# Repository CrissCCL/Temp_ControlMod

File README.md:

# 🔥 Temperature Control Module
### From System Identification to Real-Time Embedded Control

🚀 **Featured by Arduino**  
[Read the official article](https://blog.arduino.cc/2026/02/26/from-theory-to-hardware-cristian-castro-lagos-on-control-engineering-with-arduino/)

Engineering-grade closed-loop temperature control platform integrating ARX system identification, digital PI controller design, deterministic real-time implementation, and experimental validation using Arduino Leonardo.

## 🔎 Why This Project Matters

This platform demonstrates the complete professional workflow used in real-world control system development:

Data acquisition → System identification → Controller design → Discretization → Embedded implementation → Experimental validation.

It bridges control theory with physical hardware under real sampling, saturation, and noise constraints.

## 📖 Overview
This low-cost module was designed and built to perform hands-on experiments in Digital Control. The system is controlled using an Arduino Leonardo, heat is modulated with a TIP31C transistor, and temperature is measured using a TMP36 sensor.  

It provides a simple and practical platform for learning control theory in a laboratory environment.

## 📂 Contents
- `/HardwareV2` → New Version schematic, Gerbers and BOM+POS for PCBA.
- `/Hardware` → schematic, PCB, Gerbers.
- `/control_temp_LC` → C code for Arduino.

## 🌐 YouTube
📺 [Part 1 [ES]](https://youtu.be/2oqOS14WYN8?si=qGYRzMjagaLqCLr8)

## 📊 Project Status

| Component | Status |
|------------|--------|
| Temperature Sensor Interface | ✅ Completed |
| Signal Filtering and Smoothing | ✅ Completed |
| PID Control Implementation | ✅ Completed |
| Migration from MATLAB Data Logging to Processing 4 GUI | ✅ Completed |
| Data Storage and CSV Export | ✅ Completed  |
| Processing 4 GUI (Monitoring & Logging) | ✅ Completed |
|  PCB Design with Improved Measurement Stability  | ✅ Completed |

> 💻 The project now features a Processing 4 graphical interface that replaces the previous MATLAB-based monitoring, data recording and data logging system.  
> 🔧 This new GUI allows real-time temperature monitoring and data recording, alongside the ongoing development of a custom PCB to improve measurement stability and reduce signal noise.

## ⚙️ System Description
- **Controller:** Arduino Leonardo or Mega  
- **Sensor:** TMP36 analog temperature sensor  
- **Actuator:** TIP31C transistor controlling a heating element  
- **Control Strategy:** Digital PI temperature regulation  
- **Sampling period:** 0.1 seconds  
- **Data transmission:** Serial communication for data logging and Processing 4 GUI monitoring  
- **PCB:** Custom-designed board for power and measurement stability  

## 🔄 Control Loop

### Controlled Variables
- **Temperature** → Temperature value control (stabilization)

## 📐 Digital PID Control

The PID controllers implemented in this project are **incremental (velocity form)** and use **trapezoidal integration** for the integral term.  
This ensures:
- Accurate discrete-time implementation suitable for microcontrollers.
- Consistency between simulation and embedded hardware behavior.
- Avoidance of integral windup when combined with actuator saturation or anti-windup mechanisms.

The Module uses a discrete PI controller implemented on a Arduino microcontroller.  
The control law in the digital domain is expressed as:

$$
u(n) = u(n-1) + K_0 e(n) + K_1 e(n-1)
$$

Digital PI controller implemented for temperature measured,

$$
V_{PWM}(n) = V_{PWM}(n-1) + K_0 e(n) + K_1 e(n-1)
$$

### Parameters:
The parameters are adjusted for temperature measured,

$$
K_0 = K_p + \frac{K_p}{2T_i} T_s
$$

$$
K_1 = -K_p + \frac{K_p}{2T_i} T_s
$$

## 🔉 Signal Processing: Low-Pass IIR Filter (1st Order)

To reduce measurement noise, a **first-order IIR low-pass filter** was applied to the temperature signal before feeding it to the controller and the ARX model.  

### 🔹 Filter Equation  

$$
y(k) =(1 - \alpha)  \cdot x(k) +  \alpha \cdot y(k-1)
$$  

Where:  
- $$x(k)$$: raw sensor measurement at time step $$k$$  
- $$y(k)$$: filtered output  
- $$\alpha$$: smoothing factor, $$(0<\alpha<1)$$ 

## 🧪 PI Control Test and ARX Model Comparison  

A test was performed using a **PI controller** applied to the temperature control module.  
The experimental results were compared against a **linear ARX model** identified from system data.  

### 🔹 General ARX Model Equation  

The ARX (Auto-Regressive with eXogenous input) model is defined as:  

$$
y(k) + a_1 y(k-1) + a_2 y(k-2) + \dots + a_{n_a} y(k-n_a) =
b_1 u(k-1) + b_2 u(k-2) + \dots + b_{n_b} u(k-n_b) + e(k)
$$  

Where:  
- $$y(k)$$: system output at sample $$k$$ 
- $$u(k)$$: input signal at sample $$k$$  
- $$( a_i, b_j)$$: ARX parameters  
- $$( n_a, n_b)$$: model orders  
- $$e(k) $$: disturbance/noise  

### 🔹 Results Overview  
- ✅ The PI controller improved **temperature tracking** and reduced overshoot.  
- 📉 The ARX model captured the main dynamics, with small discrepancies due to nonlinear heat transfer effects.  
- ⚖️ The comparison confirms the applicability of ARX models for **thermal system control design**.  

### 🔹 Experimental Plots  

## 🖥️ GUI — Monitoring and Data Logging

The graphical user interface (GUI) shown in the photograph is developed using **Processing 4**.  
It is designed **only for monitoring** the temperature module in real time and for **recording experimental data**.  

Key features:
- Real-time plot of temperature and setpoint.
- Display of control output (PWM or equivalent).
- Logging of measurements to files for offline analysis.
- Simple visualization of system behavior during experiments.

> ⚠️ **Note:** The GUI is for observation and data recording only; it does **not** modify the control system or send commands to the hardware.

> ⚠️ **Status:** Work In Progress — the GUI is being actively developed and will be added to the repository once sufficiently stable.

## 📉 Measurement Stability Improvement — PCB v2 vs PCB v3

The new PCB revision focused on improving the **temperature signal stability** without changing the control algorithm.

### 🔧 Issues Observed in PCB v2
In the previous revision, the temperature reading from the TMP36 sensor showed perturbations during heater actuation by the TIP31C transistor.  
This was mainly due to lack of proper analog stabilization near the sensor.

### ✅ Modifications Introduced in PCB v3
To address this, the following hardware changes were implemented according to TMP36 manufacturer guidelines:

- ✔ **Decoupling capacitor added** close to TMP36 power pins
- ✔ **Analog conditioning resistors changed to SMD**
- ✔ **All related passive components migrated to SMD footprint** to minimize parasitics and noise pickup

No changes were made to the controller firmware or sensor type — only the PCB-level conditioning was improved.

### 📊 Comparative Experimental Results

| Version | Condition | Plot |
|--------|------------|------|
| **PCB v2 (Old)** | Visible ripple & switching noise on temperature signal |  |
| **PCB v3 (New)** | Stable and smooth measurement — disturbances eliminated |  |

> ✅ The addition of the capacitor and SMD passives significantly reduced noise, improving the quality of temperature measurements and the overall stability of the closed-loop response.

## 🖼️ Render 3D PCB 

<table>
  <tr>
    <td align="center">
      <br>
      <sub>PCB Render - Version 3 - NEW VERSION </sub>
    </td>
    <td align="center">
        <br>
      <sub>PCB Render - Version 2- OLDER VERSION </sub>
    </td>
  </tr>
</table>

## ⚡ Physical Prototype

The updated PCB and system assembly have been tested successfully.  
The following image shows the complete setup of the **new prototype version**:

The following images show the complete setup of the **previous prototype version**:

<table>
  <tr>
    <td align="center">
      <br>
      <sub>Device connections</sub>
    </td>
    <td align="center">
      <br>
      <sub>Complete setup</sub>
    </td>
  </tr>
</table>

## 🔗 ROS 2 Integration

This embedded temperature control module can be connected to a ROS 2 system
for supervision, telemetry streaming, remote setpoint control and online metrics.

👉 **ROS 2 Bridge Repository:**  
[Ros integration](https://github.com/CrissCCL/Temp_ControlMod_ROS_integration)

The ROS integration provides:

- UART ↔ ROS 2 bridge
- Real-time topics (/temp, /u, /ref)
- Remote setpoint commands
- Online control performance metrics (IAE, ISE, ITAE, etc.)
- rosbag logging and visualization tools

This separation keeps:
- this repo → embedded/firmware/control
- ROS repo → middleware/supervision/integration

## 🔗 Related Repositories

For additional tutorials and examples related to digital control simulations, visit:

- [Digital Control — Anti-Windup (Positional PI)](https://github.com/CrissCCL/Digital_ControlAntiWindup)
- [Digital Control Simulation — First Order System + Saturation](https://github.com/CrissCCL/Digital_ControlSim)
- [Digital Control Simulation — ARX Model + Saturation](https://github.com/CrissCCL/Digital_ControlSimARX)

## 🤝 Support projects
 Support me on Patreon [https://www.patreon.com/c/CrissCCL](https://www.patreon.com/c/CrissCCL)

## 📜 License
MIT License

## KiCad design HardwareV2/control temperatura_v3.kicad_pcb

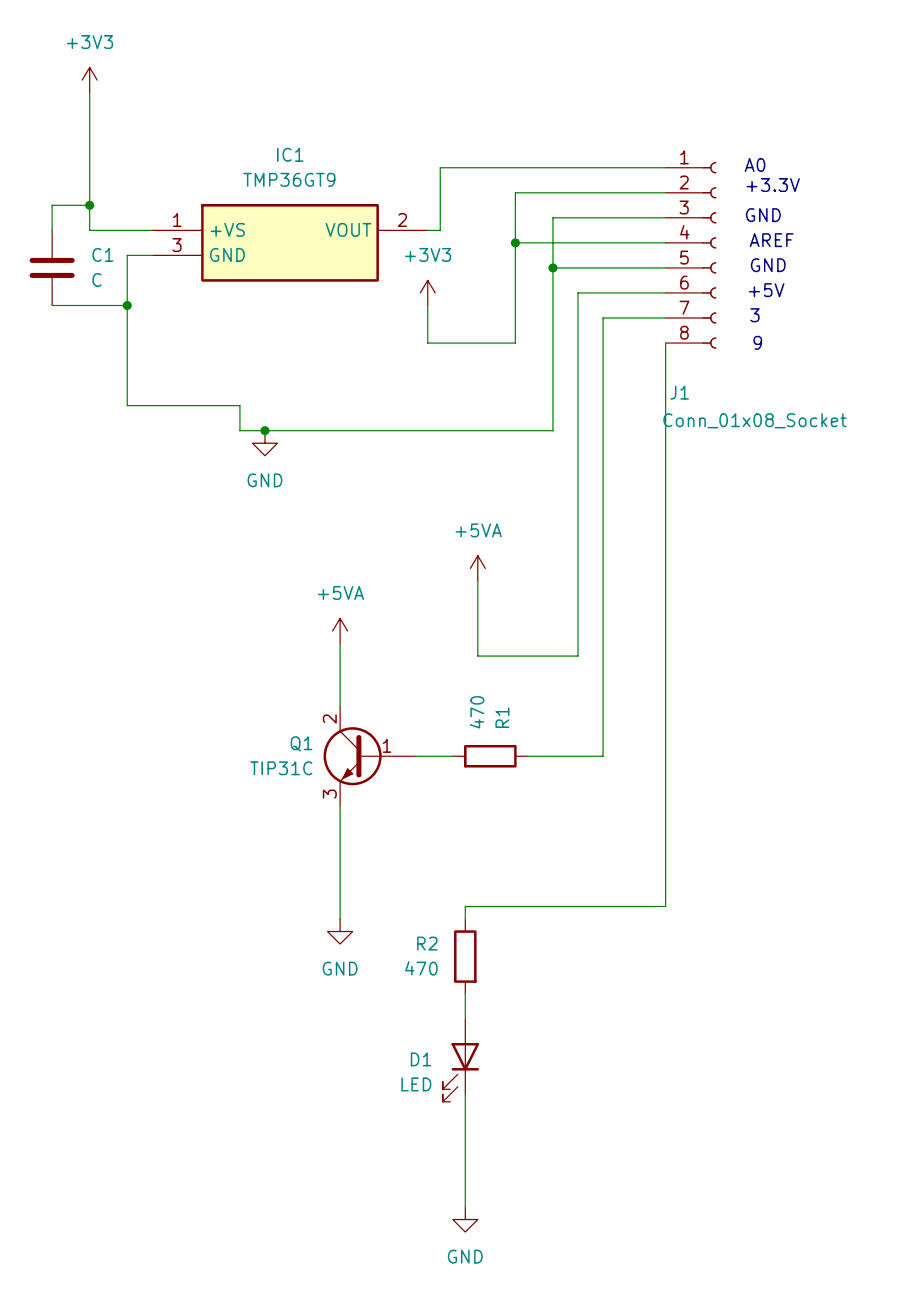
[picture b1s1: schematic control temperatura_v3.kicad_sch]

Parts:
C1: C; C_1206_3216Metric_Pad1.33x1.80mm_HandSolder
D1: LED; LED_D5.0mm
IC1: TMP36GT9; Manufacturer_Part_Number TMP36GT9; Mouser Part Number 584-TMP36GT9
J1: Conn_01x08_Socket; PinHeader_1x08_P2.54mm_Vertical
Q1: TIP31C; TO-220-3_Vertical
R1, R2: 470; R_1206_3216Metric_Pad1.30x1.75mm_HandSolder

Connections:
+3V3: C1.1, IC1.1 (+VS), J1.2, J1.4
+5VA: J1.6, Q1.2 (C)
GND: C1.2, D1.1 (K), IC1.3 (GND), J1.3, J1.5, Q1.3 (E)
unnamed: D1.2 (A), R2.2
unnamed: IC1.2 (VOUT), J1.1
unnamed: J1.7, R1.1
unnamed: J1.8, R2.1
unnamed: Q1.1 (B), R1.2

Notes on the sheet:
+5V
GND
+3.3V
AREF

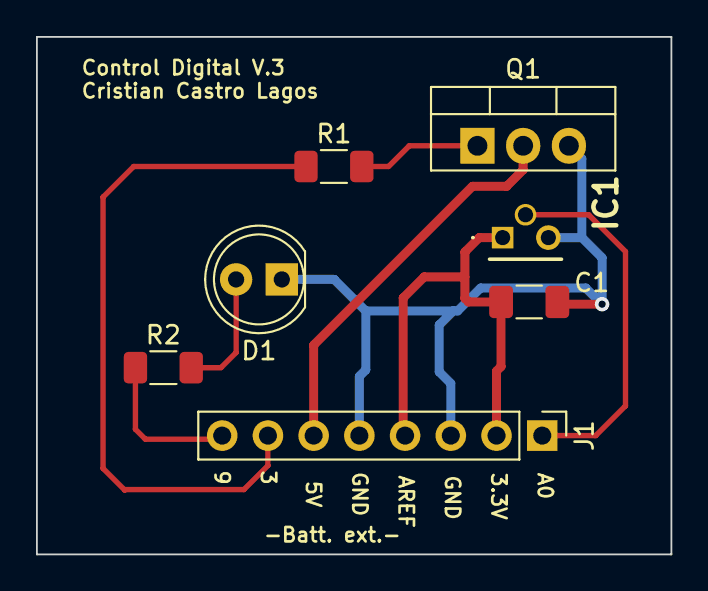
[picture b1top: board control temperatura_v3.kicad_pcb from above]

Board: 2 copper layers, 35.2 x 28.8 mm, 7 parts (0 on the bottom side), 8 nets.

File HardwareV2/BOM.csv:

"Reference","Qty","Value","DNP","Exclude from BOM","Exclude from Board","Footprint","Datasheet"
"C1","1","C","","","","Capacitor_SMD:C_1206_3216Metric_Pad1.33x1.80mm_HandSolder","~"
"D1","1","LED","","","","LED_THT:LED_D5.0mm","~"
"IC1","1","TMP36GT9","","","","SamacSys_Parts:TMP36GT9","https://www.analog.com/media/en/technical-documentation/data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"
"J1","1","Conn_01x08_Socket","","","","Connector_PinHeader_2.54mm:PinHeader_1x08_P2.54mm_Vertical","~"
"Q1","1","TIP31C","","","","Package_TO_SOT_THT:TO-220-3_Vertical","https://www.centralsemi.com/get_document.php?cmp=1&mergetype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"
"R1,R2","2","470","","","","Resistor_SMD:R_1206_3216Metric_Pad1.30x1.75mm_HandSolder","~"

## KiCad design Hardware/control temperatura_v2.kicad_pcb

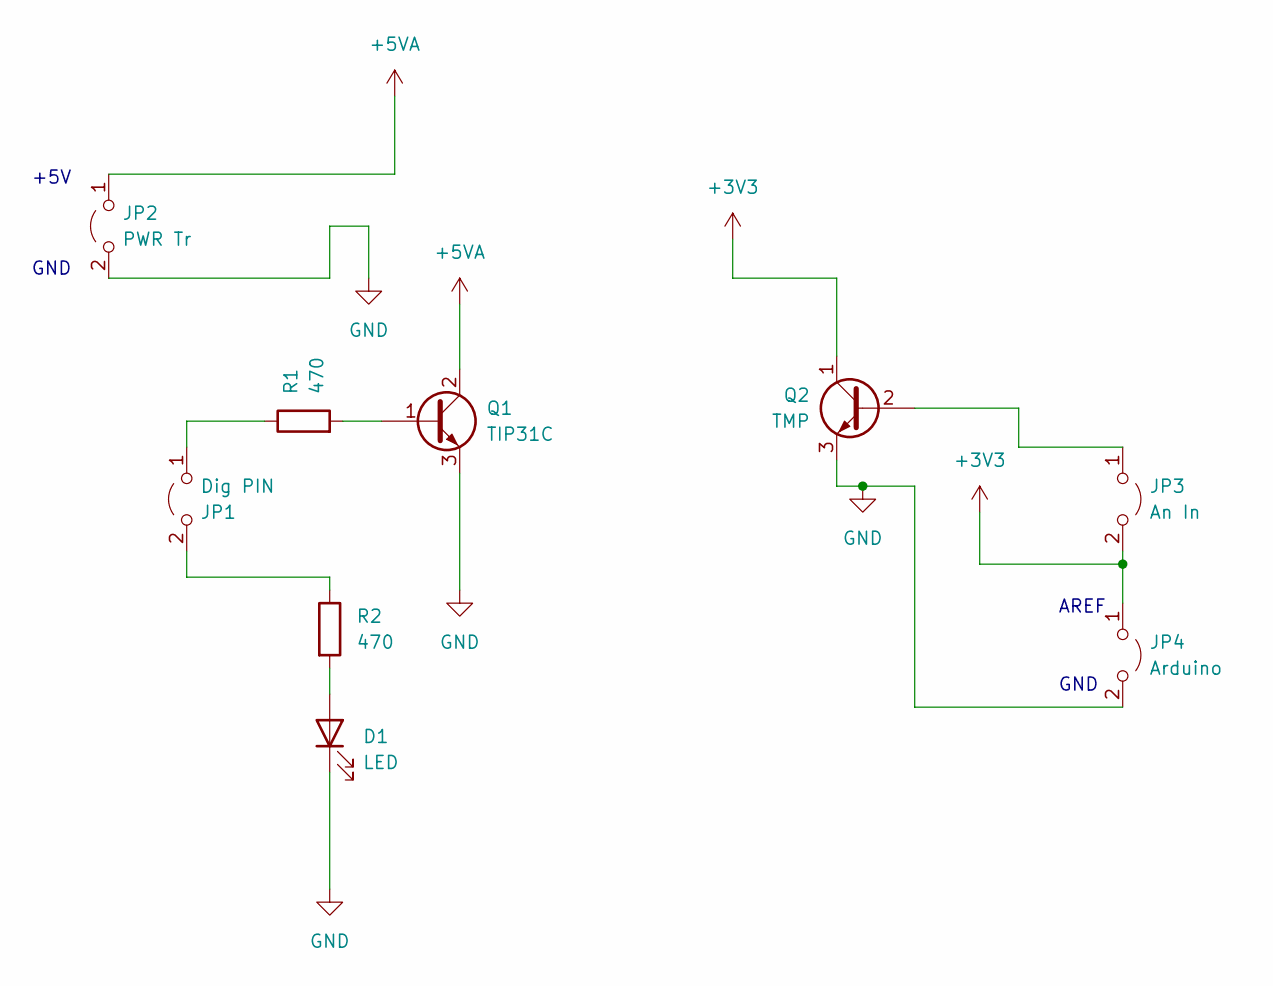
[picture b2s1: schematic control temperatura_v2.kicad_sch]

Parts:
D1: LED; LED_D5.0mm
JP1: Dig PIN; TestPoint_2Pads_Pitch2.54mm_Drill0.8mm
JP2: PWR Tr; TestPoint_2Pads_Pitch2.54mm_Drill0.8mm
JP3: An In; TestPoint_2Pads_Pitch2.54mm_Drill0.8mm
JP4: Arduino; TestPoint_2Pads_Pitch2.54mm_Drill0.8mm
Q1: TIP31C; TO-220-3_Vertical
Q2: TMP; TO-92_Inline
R1, R2: 470; R_Axial_DIN0207_L6.3mm_D2.5mm_P10.16mm_Horizontal

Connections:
+3V3: JP3.2 (B), JP4.1 (A), Q2.1 (C)
+5VA: JP2.1 (A), Q1.2 (C)
GND: D1.1 (K), JP2.2 (B), JP4.2 (B), Q1.3 (E), Q2.3 (E)
unnamed: D1.2 (A), R2.2
unnamed: JP1.1 (A), R1.1
unnamed: JP1.2 (B), R2.1
unnamed: JP3.1 (A), Q2.2 (B)
unnamed: Q1.1 (B), R1.2

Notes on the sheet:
+5V
GND
AREF

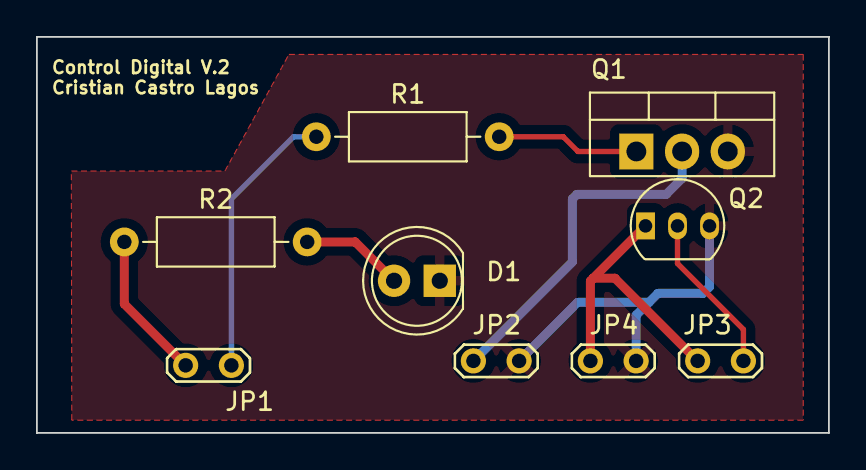
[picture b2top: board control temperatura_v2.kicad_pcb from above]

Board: 2 copper layers, 44.0 x 22.0 mm, 9 parts (0 on the bottom side), 8 nets.

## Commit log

2025-09-25 Create LICENSE
2025-09-25 Update and rename LICENSE to LICENSE 2
2025-09-26 Rename esquema_control.png to procesotemp.png
2025-09-30 Rename controlSim_exp2.png to controlSim_Exp2.png
2025-10-22 Update README with new PCB Render - Version 2
    Added PCB Render - Version 2 image to the README.
2025-10-23 Clean up README formatting
    Removed unnecessary line breaks in README.
2025-10-24 Rename esquema control temp.png to esquema_control_temp.png
2025-10-24 Update image links to use raw GitHub URLs
2025-10-24 Change diagram image width from 500 to 600
    Updated image size in control loop diagram.
2025-10-24 Adjust image width in Control Loop section
    Updated image size in Control Loop diagram.
2025-10-24 Adjust image widths for PCB comparison in README
    Updated image widths in comparative results section.
2025-10-24 Adjust image width for PCB v2 in README
    Updated image width for PCB v2 (Old) in comparative results.
2026-01-05 Fix typo in 'Support project' heading
2026-02-07 Update LICENSE
2026-02-24 Add section on system identification and control
2026-02-26 Improve README formatting for featured article
    Updated the README to enhance the presentation of the featured article.
